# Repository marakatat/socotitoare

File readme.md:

# Socotitoare
The new, refined, 4-button keypad with a rotary encoder that is the best for everything. The project was harder than I thought. I finished after 3 weeks of work, and I thought it would take me like 2 days... Maybe if I hadn't switched between so many CAD tools. KiCAD is the best program to use btw, very intuitive, very good, very nice, Romanian approved. :like:

# Why?
To be honest, I like free stuff. I wanted to design my own things but I didn't have the motivation to start anything because I didn't know anything related. (secret project incoming). When I saw the "Blueprint" idea, I believed that was my moment, and here we are.

# How to use
Plug in a usb type C cable. The keys and knob will be programable through [Input Remapper](https://github.com/sezanzeb/input-remapper).

# BOM

| Part | Quantity | Link |
| :--- | :--- | :--- |
| Cherry MX Switch | 4 | [Link](https://www.aliexpress.com/item/1005006255961111.html) |
| Rotary Encoder (EC11) | 1 | [Link](https://www.aliexpress.com/item/1005010054024165.html) |
| Keycaps | 4 | [Link](https://www.aliexpress.com/item/32842379355.html) |
| OLED Display (SSD1306) | 1 | [Link](https://www.aliexpress.com/item/1005006365845676.html) |
| Microcontroller (XIAO RP2040) | 1 | [Link](https://www.aliexpress.com/item/1005003682505451.html) |
| Diodes (1N4148) | 5 | [Link](https://www.aliexpress.com/item/1005004962400215.html) |
| Leds (SK6812MINI) | 5 | [Link](https://www.aliexpress.com/item/1005001971806517.html) |

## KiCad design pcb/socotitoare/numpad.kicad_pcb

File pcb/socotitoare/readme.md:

The pcb was easy to make but hard to design, to get the best ergonomics and all that jazz for me. As I said in the main readme, KiCAD is the best, the shit. It is romanian approved. :like: si aici

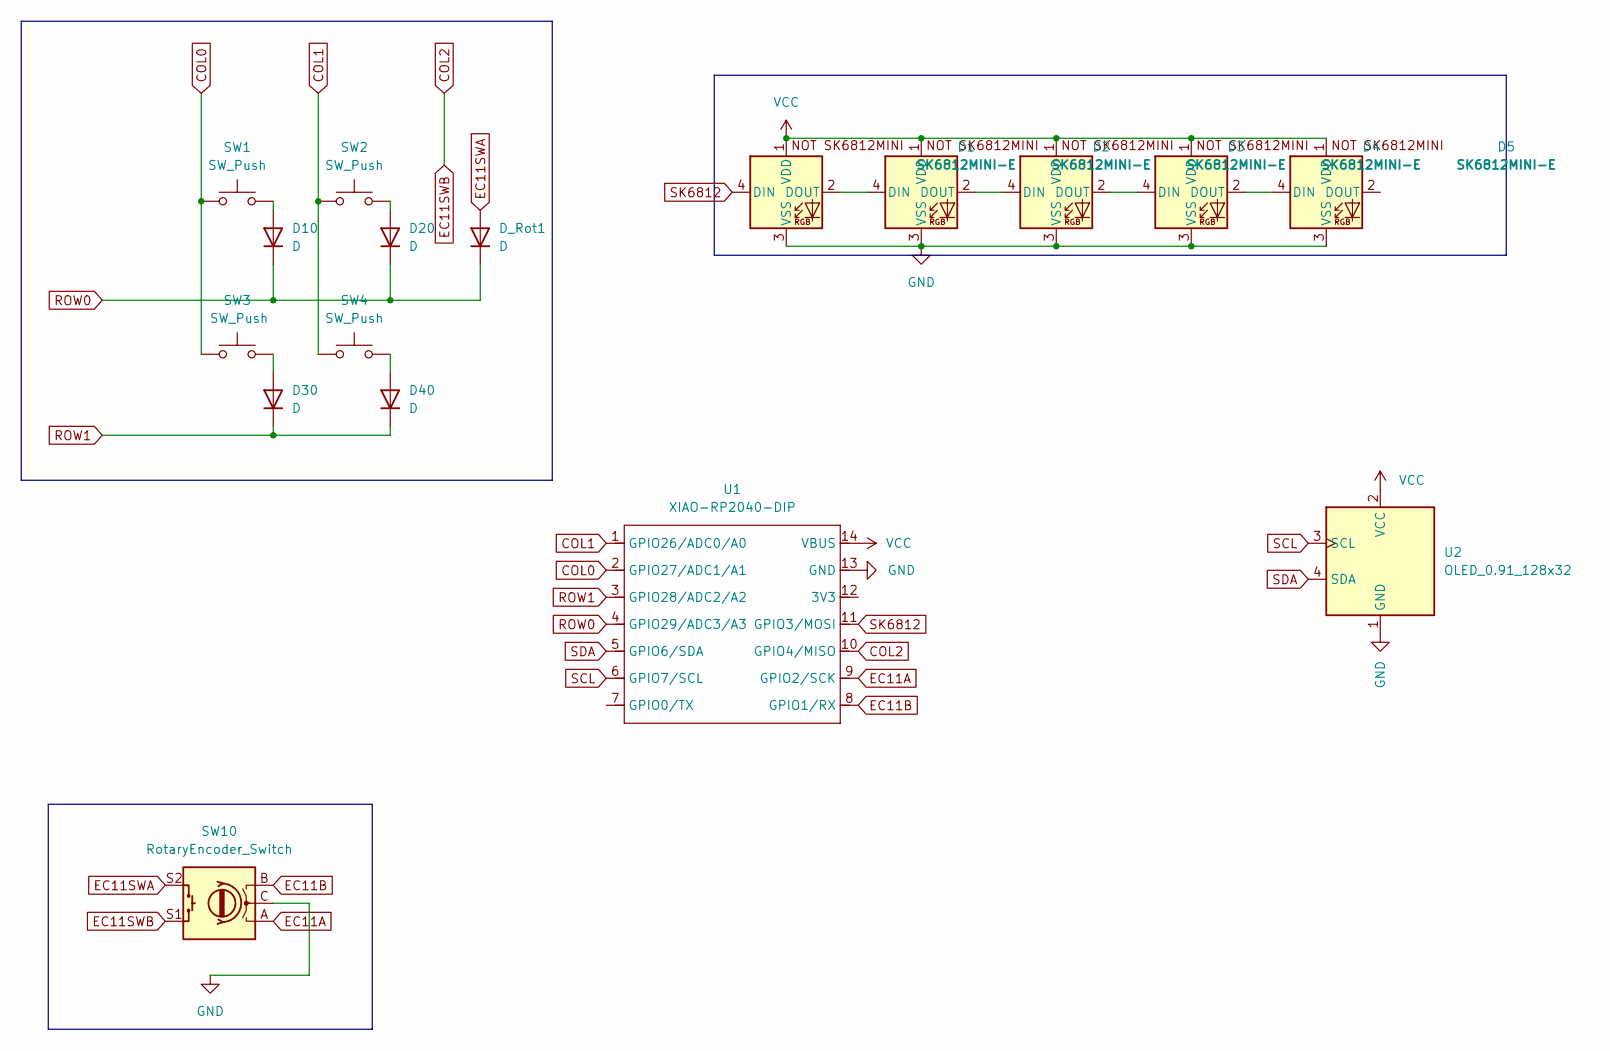
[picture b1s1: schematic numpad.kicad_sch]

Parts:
D1, D2, D3, D4, D5: SK6812MINI-E; MX_SK6812MINI-E_REV
D10, D20, D30, D40: D; D_DO-35_SOD27_P7.62mm_Horizontal
D_Rot1: D; D_DO-35_SOD27_P7.62mm_Horizontal
SW1, SW2, SW3, SW4: SW_Push; SW_Cherry_MX_1.00u_PCB
SW10: RotaryEncoder_Switch; RotaryEncoder_Alps_EC11E-Switch_Vertical_H20mm
U1: XIAO-RP2040-DIP
U2: OLED_0.91_128x32

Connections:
COL0: SW1.1, SW3.1, U1.2 (GPIO27/ADC1/A1)
COL1: SW2.1, SW4.1, U1.1 (GPIO26/ADC0/A0)
COL2: SW10.S1, U1.10 (GPIO4/MISO)
EC11A: SW10.A, U1.9 (GPIO2/SCK)
EC11B: SW10.B, U1.8 (GPIO1/RX)
EC11SWA: D_Rot1.2 (A), SW10.S2
GND: D1.3 (VSS), D2.3 (VSS), D3.3 (VSS), D4.3 (VSS), D5.3 (VSS), SW10.C, U1.13 (GND), U2.1 (GND)
unnamed: D1.2 (DOUT), D2.4 (DIN)
unnamed: D2.2 (DOUT), D3.4 (DIN)
unnamed: D3.2 (DOUT), D4.4 (DIN)
unnamed: D4.2 (DOUT), D5.4 (DIN)
unnamed: D10.2 (A), SW1.2
unnamed: D20.2 (A), SW2.2
unnamed: D30.2 (A), SW3.2
unnamed: D40.2 (A), SW4.2
ROW0: D10.1 (K), D20.1 (K), D_Rot1.1 (K), U1.4 (GPIO29/ADC3/A3)
ROW1: D30.1 (K), D40.1 (K), U1.3 (GPIO28/ADC2/A2)
SCL: U1.6 (GPIO7/SCL), U2.3 (SCL)
SDA: U1.5 (GPIO6/SDA), U2.4 (SDA)
SK6812: D1.4 (DIN), U1.11 (GPIO3/MOSI)
VCC: D1.1 (VDD), D2.1 (VDD), D3.1 (VDD), D4.1 (VDD), D5.1 (VDD), U1.14 (VBUS), U2.2 (VCC)

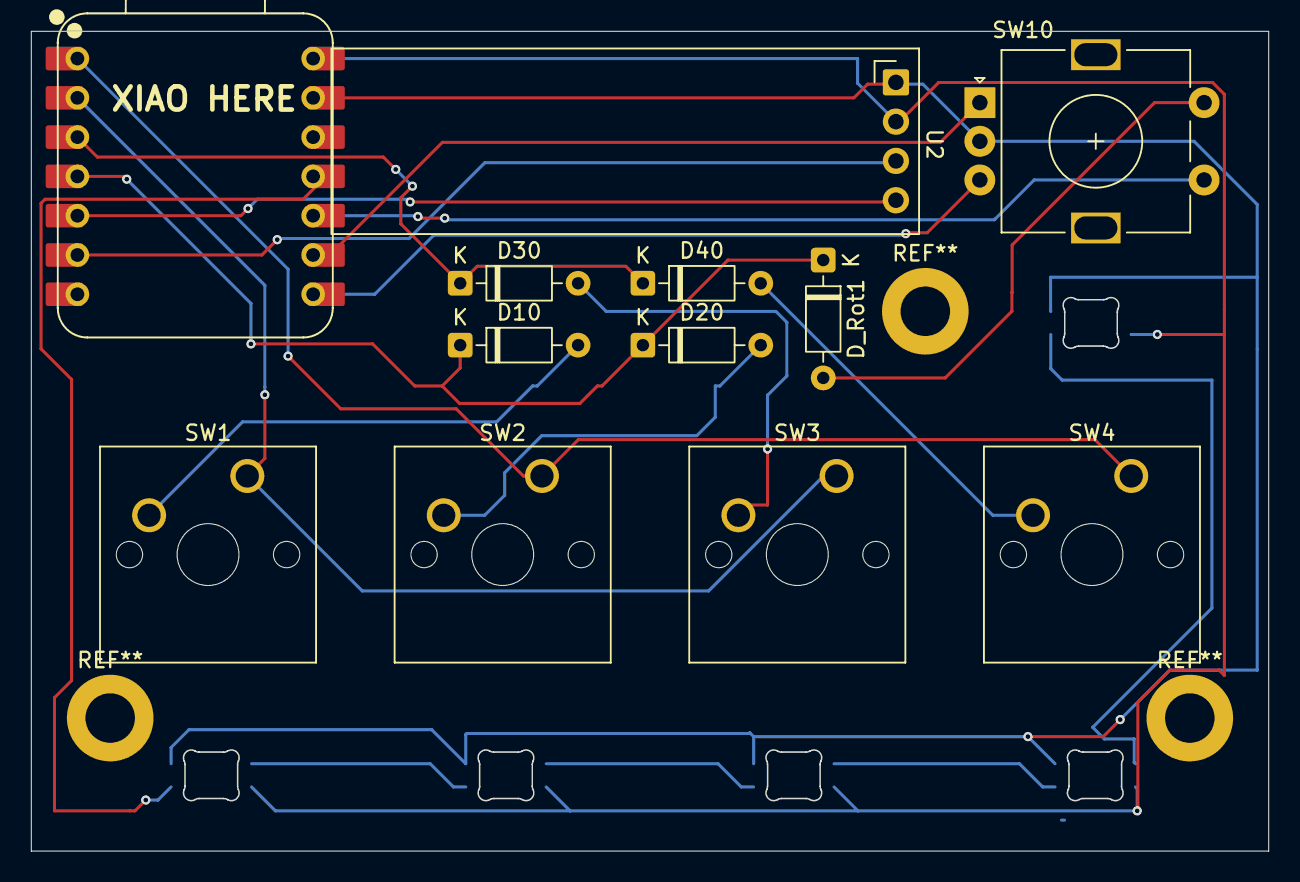
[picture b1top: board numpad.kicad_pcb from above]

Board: 2 copper layers, 80.0 x 53.0 mm, 17 parts (0 on the bottom side), 21 nets.

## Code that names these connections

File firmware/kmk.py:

import board

from kmk.kmk_keyboard import KMKKeyboard
from kmk.keys import KC
from kmk.scanners import DiodeOrientation
from kmk.modules.encoder import EncoderHandler
from kmk.modules.layers import Layers
from kmk.extensions.media_keys import MediaKeys
from kmk.extensions.RGB import RGB

keyboard = KMKKeyboard()

# Enables the Media Keys extension for volume control
keyboard.extensions.append(MediaKeys())

# --- Matrix Configuration ---
# Cols: COL0=D27, COL1=D26, COL2=D4
# Rows: ROW0=D29, ROW1=D28 
# Diodes point from Col to Row (COL2ROW)
keyboard.col_pins = (board.D27, board.D26, board.D4)
keyboard.row_pins = (board.D29, board.D28)
keyboard.diode_orientation = DiodeOrientation.COL2ROW

# --- Rotary Encoder Configuration ---
# Encoder pins: A=D2, B=D1
# The encoder switch is in the matrix at (ROW0, COL2)
encoder_handler = EncoderHandler()
keyboard.modules.append(encoder_handler)
encoder_handler.pins = ((board.D2, board.D1, None, False),)

# --- RGB Configuration ---
# SK6812 LEDs on D3
# Mapping: Key 0->LED 0 ... Key 4->LED 4
rgb = RGB(pixel_pin=board.D3, num_pixels=5, val_limit=100, hue_default=0, sat_default=255, val_default=100)
keyboard.extensions.append(rgb)

# --- Coordinate Mapping ---
# Reorders logical keys to match LED order: SW1, SW2, SW3, SW4, Enc
# Matrix Scan Order (Cols D27, D26, D4; Rows D29, D28):
# 0: R0-C0 (SW1) -> Map 0
# 1: R0-C1 (SW2) -> Map 1
# 2: R0-C2 (Enc) -> Map 4 (Last)
# 3: R1-C0 (SW3) -> Map 2
# 4: R1-C1 (SW4) -> Map 3
# 5: R1-C2 (Empty)-> Map 5
keyboard.coord_mapping = [
    0,  # SW1
    1,  # SW2
    4,  # Enc
    2,  # SW3
    3,  # SW4
    5   # Empty
]

# --- Keymap ---
# Logical Order: SW1, SW2, SW3, SW4, Enc, Empty
keyboard.keymap = [
    [
        KC.N7,    # SW1
        KC.N8,    # SW2
        KC.N4,    # SW3
        KC.N5,    # SW4
        KC.MUTE,  # Enc Switch
        KC.NO,    # Empty
    ]
]

# Encoder Rotation Map
encoder_handler.map = [
    ((KC.VOLD, KC.VOLU, KC.NO),),
]

if __name__ == '__main__':
    keyboard.go()

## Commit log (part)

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2026-02-03 socotitoare
2026-02-03 readme
2026-02-03 read
2026-02-07 v2 final
